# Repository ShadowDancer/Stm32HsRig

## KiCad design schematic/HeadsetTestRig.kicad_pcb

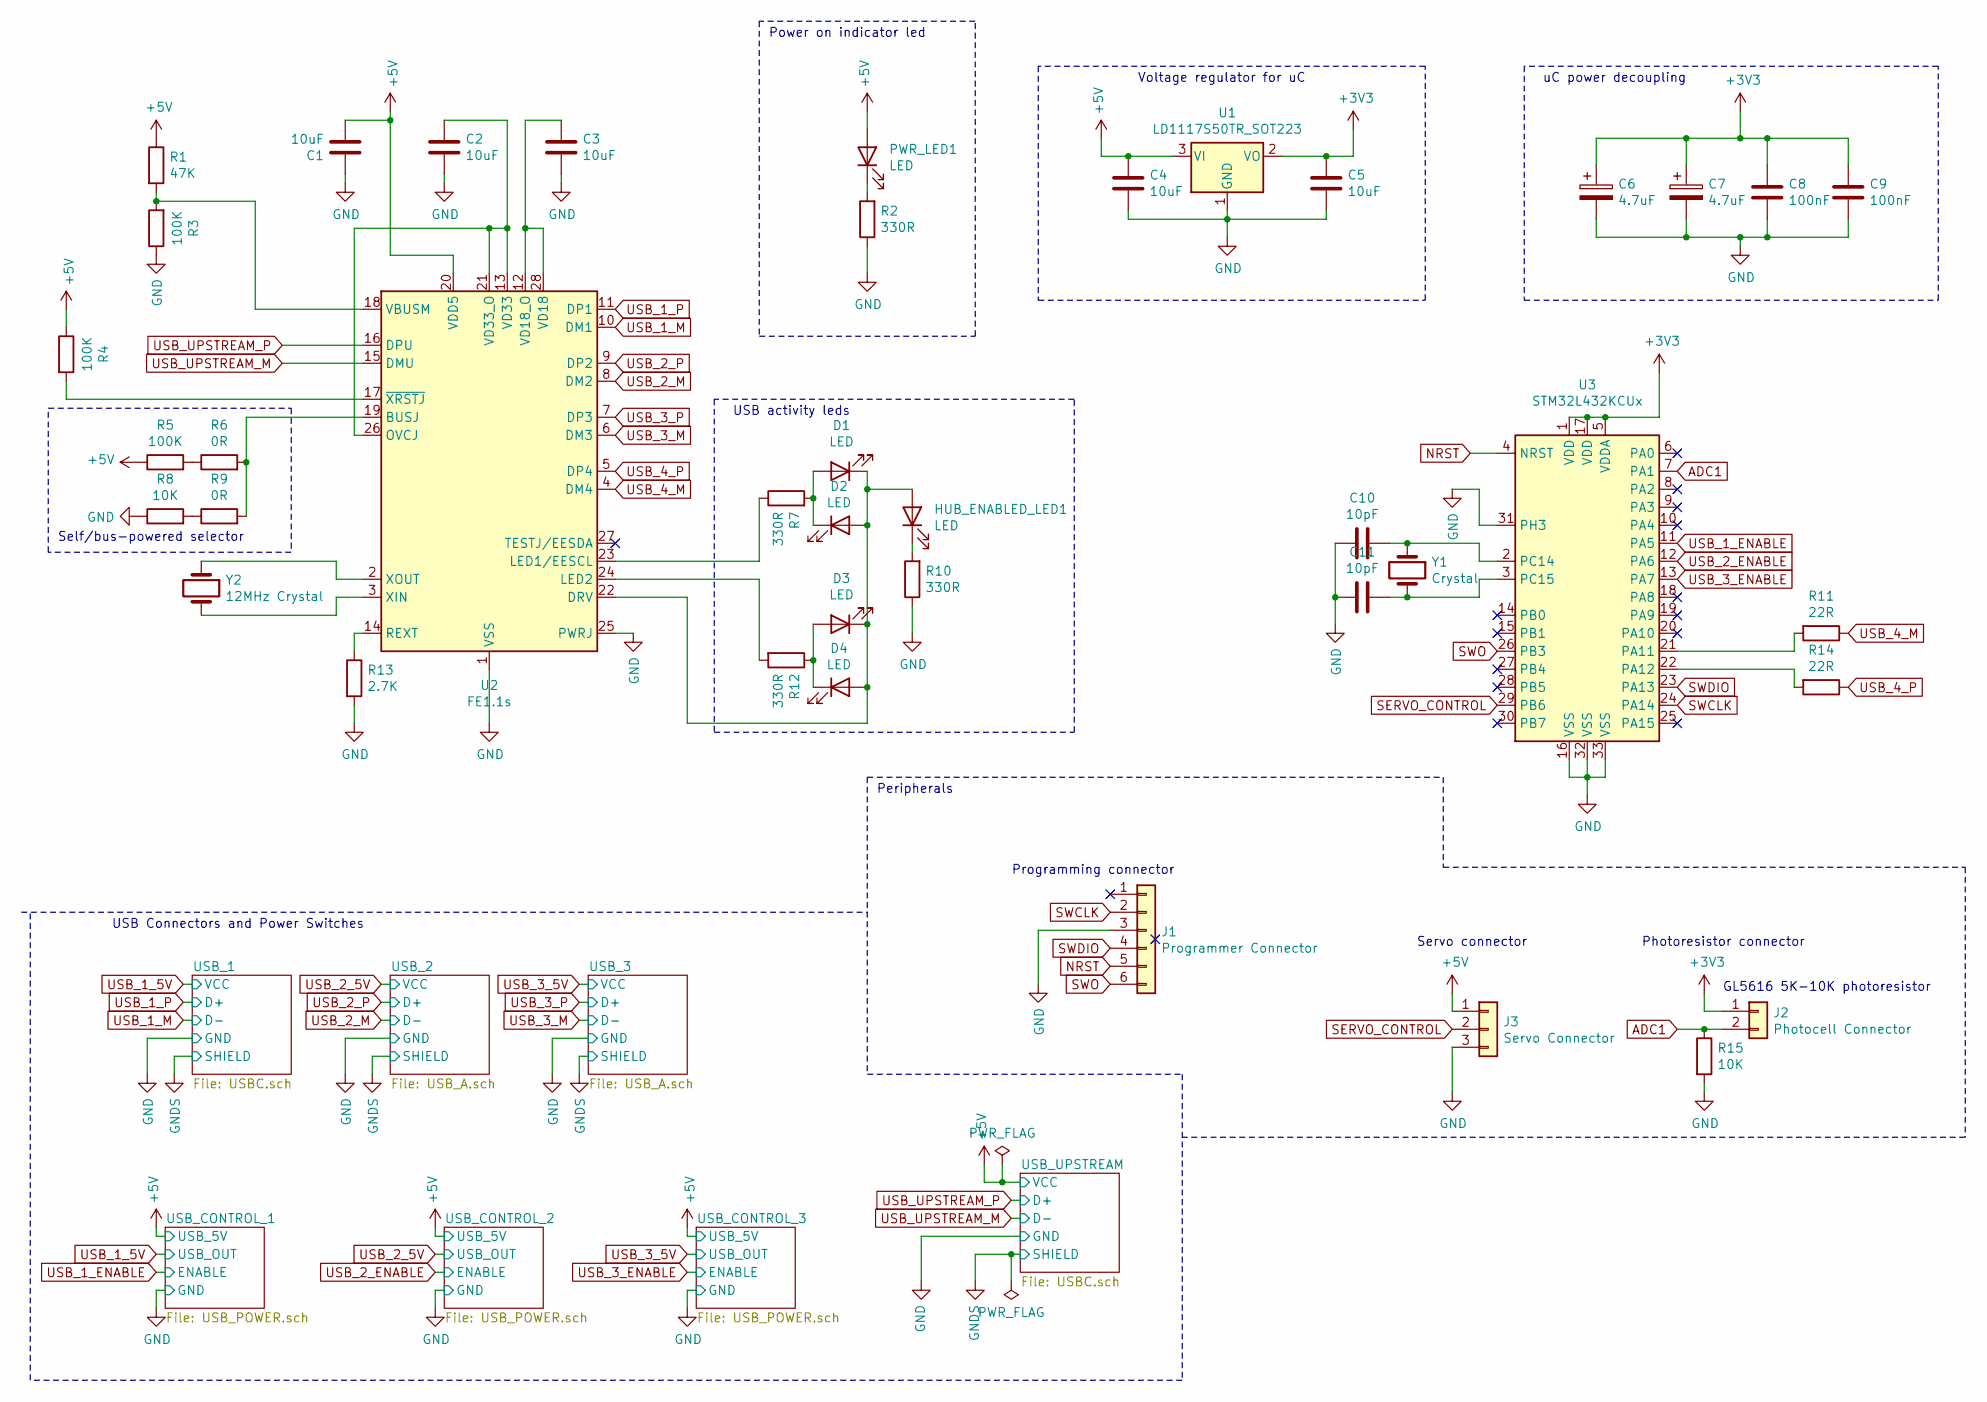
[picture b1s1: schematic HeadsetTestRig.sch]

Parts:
C1, C2, C3, C4, C5: 10uF; C_1206_3216Metric
C6, C7: 4.7uF; C_1206_3216Metric
C8, C9: 100nF; C_1206_3216Metric
C10, C11: 10pF; C_1206_3216Metric
D1, D2, D3, D4: LED; LED_1206_3216Metric
HUB_ENABLED_LED1: LED; LED_1206_3216Metric
J1: Programmer Connector; PinHeader_1x06_P2.54mm_Vertical
J2: Photocell Connector; JST_PH_B2B-PH-K_1x02_P2.00mm_Vertical
J3: Servo Connector; JST_PH_B3B-PH-K_1x03_P2.00mm_Vertical
PWR_LED1: LED; LED_1206_3216Metric
R1: 47K; R_0805_2012Metric
R2, R7, R10, R12: 330R; R_1206_3216Metric
R3, R5: 100K; R_0805_2012Metric
R4: 100K; R_1206_3216Metric
R6, R9: 0R; R_0805_2012Metric
R8: 10K; R_0805_2012Metric
R11, R14: 22R; R_1206_3216Metric
R13: 2.7K; R_0805_2012Metric
R15: 10K; R_1206_3216Metric
U1: LD1117S50TR_SOT223; SOT-223-3_TabPin2
U2: FE1.1s; SSOP-28_3.9x9.9mm_P0.635mm
U3: STM32L432KCUx; QFN-32-1EP_5x5mm_P0.5mm_EP3.45x3.45mm
Y1: Crystal; Crystal_HC49-U_Vertical
Y2: 12MHz Crystal; Crystal_HC49-U_Vertical

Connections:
+3V3: C5.1, C6.1, C7.1, C8.1, C9.1, J2.1, U1.2 (VO), U3.1 (VDD), U3.5 (VDDA), U3.17 (VDD)
+5V: C1.2, C4.1, J3.1, PWR_LED1.2 (A), R1.1, R4.1, R5.1, U1.3 (VI), U2.20 (VDD5); also elsewhere on the board
ADC1: J2.2, R15.1, U3.7 (PA1)
GND: C1.1, C2.2, C3.2, C4.2, C5.2, C6.2, C7.2, C8.2, C9.2, C10.2, C11.2, J1.3, J3.3, R2.1, R3.1, R8.1, R10.1, R13.2, R15.2, U1.1 (GND), U2.1 (VSS), U2.25 (PWRJ), U3.16 (VSS), U3.31 (PH3), U3.32 (VSS), U3.33 (VSS); also elsewhere on the board
NRST: J1.5, U3.4 (NRST)
unnamed: C2.1, U2.13 (VD33), U2.21 (VD33_O), U2.26 (OVCJ)
unnamed: C3.1, U2.12 (VD18_O), U2.28 (VD18)
unnamed: C10.1, U3.2 (PC14), Y1.1
unnamed: C11.1, U3.3 (PC15), Y1.2
unnamed: D1.1 (K), D2.2 (A), D3.1 (K), D4.2 (A), HUB_ENABLED_LED1.2 (A), U2.22 (DRV)
unnamed: D1.2 (A), D2.1 (K), R7.2
unnamed: D3.2 (A), D4.1 (K), R12.1
unnamed: HUB_ENABLED_LED1.1 (K), R10.2
unnamed: PWR_LED1.1 (K), R2.2
unnamed: R1.2, R3.2, U2.18 (VBUSM)
unnamed: R4.2, U2.17 (~XRSTJ)
unnamed: R5.2, R6.1
unnamed: R6.2, R9.2, U2.19 (BUSJ)
unnamed: R7.1, U2.23 (LED1/EESCL)
unnamed: R8.2, R9.1
unnamed: R11.2, U3.21 (PA11)
unnamed: R12.2, U2.24 (LED2)
unnamed: R13.1, U2.14 (REXT)
unnamed: R14.2, U3.22 (PA12)
unnamed: U2.2 (XOUT), Y2.1
unnamed: U2.3 (XIN), Y2.2
SERVO_CONTROL: J3.2, U3.29 (PB6)
SWCLK: J1.2, U3.24 (PA14)
SWDIO: J1.4, U3.23 (PA13)
SWO: J1.6, U3.26 (PB3)
USB_1_ENABLE: U3.11 (PA5); also elsewhere on the board
USB_1_M: U2.10 (DM1); also elsewhere on the board
USB_1_P: U2.11 (DP1); also elsewhere on the board
USB_2_ENABLE: U3.12 (PA6); also elsewhere on the board
USB_2_M: U2.8 (DM2); also elsewhere on the board
USB_2_P: U2.9 (DP2); also elsewhere on the board
USB_3_ENABLE: U3.13 (PA7); also elsewhere on the board
USB_3_M: U2.6 (DM3); also elsewhere on the board
USB_3_P: U2.7 (DP3); also elsewhere on the board
USB_4_M: R11.1, U2.4 (DM4)
USB_4_P: R14.1, U2.5 (DP4)
USB_UPSTREAM_M: U2.15 (DMU); also elsewhere on the board
USB_UPSTREAM_P: U2.16 (DPU); also elsewhere on the board

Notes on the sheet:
GL5616 5K-10K photoresistor
USB Connectors and Power Switches
Self/bus-powered selector
USB activity leds
Power on indicator led
Voltage regulator for uC
uC power decoupling
Peripherals
Programming connector
Servo connector
Photoresistor connector

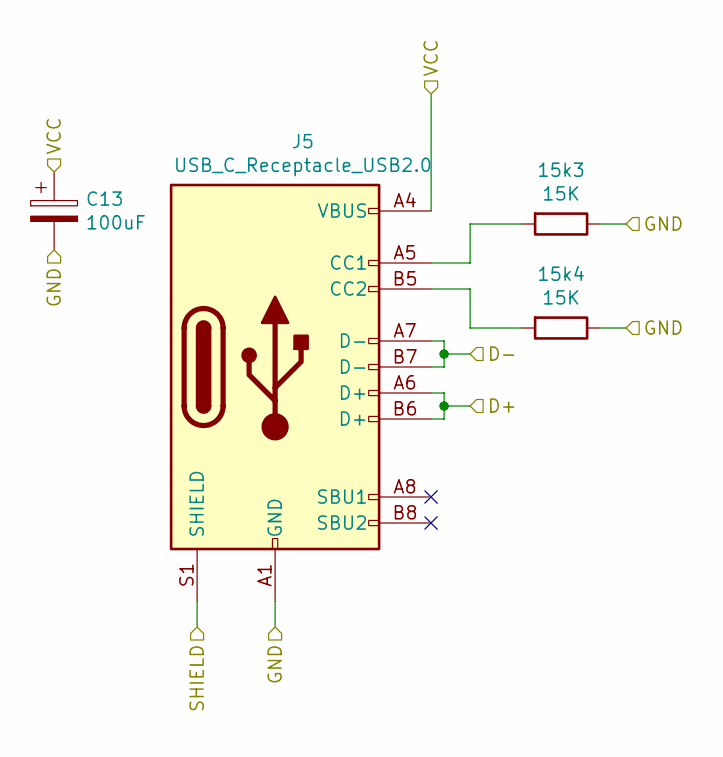
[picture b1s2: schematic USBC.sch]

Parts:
15k1, 15k2: 15K; R_0805_2012Metric
C12: 100uF; CP_Elec_6.3x5.9
J4: USB_C_Receptacle_USB2.0

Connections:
+5V: C12.1, J4.A4 (VBUS), J4.A9 (VBUS), J4.B4 (VBUS), J4.B9 (VBUS); also elsewhere on the board
GND: 15k1.1, 15k2.1, C12.2, J4.A1 (GND), J4.A12 (GND), J4.B1 (GND), J4.B12 (GND); also elsewhere on the board
GNDS: J4.S1 (SHIELD); also elsewhere on the board
unnamed: 15k1.2, J4.A5 (CC1)
unnamed: 15k2.2, J4.B5 (CC2)
USB_UPSTREAM_M: J4.A7 (D-), J4.B7 (D-); also elsewhere on the board
USB_UPSTREAM_P: J4.A6 (D+), J4.B6 (D+); also elsewhere on the board

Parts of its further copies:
15k3, 15k4: 15K; R_0805_2012Metric
C13: 100uF; CP_Elec_6.3x5.9
J5: USB_C_Receptacle_USB2.0

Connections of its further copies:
GND: 15k3.1, 15k4.1, J5.A1 (GND), J5.A12 (GND), J5.B1 (GND), J5.B12 (GND); also elsewhere on the board
GNDS: J5.S1 (SHIELD); also elsewhere on the board
unnamed: 15k3.2, J5.A5 (CC1)
unnamed: 15k4.2, J5.B5 (CC2)
USB_1_5V: J5.A4 (VBUS), J5.A9 (VBUS), J5.B4 (VBUS), J5.B9 (VBUS); also elsewhere on the board
USB_1_M: J5.A7 (D-), J5.B7 (D-); also elsewhere on the board
USB_1_P: J5.A6 (D+), J5.B6 (D+); also elsewhere on the board

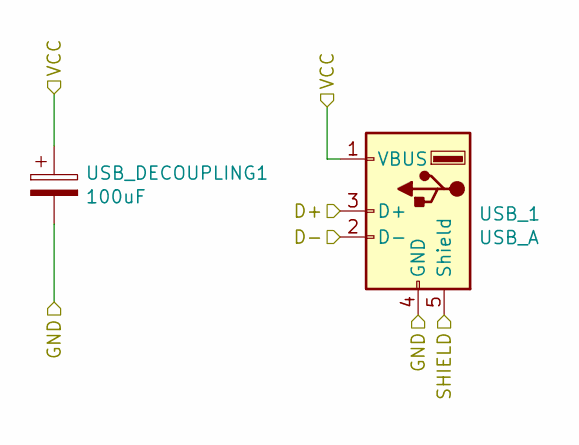
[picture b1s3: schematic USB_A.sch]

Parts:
USB_1: USB_A; USB_B_Lumberg_2411_02_Horizontal
USB_DECOUPLING1: 100uF; CP_Elec_6.3x5.9

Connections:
GND: USB_1.4 (GND), USB_DECOUPLING1.2; also elsewhere on the board
GNDS: USB_1.5 (Shield); also elsewhere on the board
USB_2_5V: USB_1.1 (VBUS), USB_DECOUPLING1.1; also elsewhere on the board
USB_2_M: USB_1.2 (D-); also elsewhere on the board
USB_2_P: USB_1.3 (D+); also elsewhere on the board

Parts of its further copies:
USB_2: USB_A; USB_B_Lumberg_2411_02_Horizontal
USB_DECOUP2: 100uF; CP_Elec_6.3x5.9

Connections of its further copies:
GND: USB_2.4 (GND), USB_DECOUP2.2; also elsewhere on the board
GNDS: USB_2.5 (Shield); also elsewhere on the board
USB_3_5V: USB_2.1 (VBUS), USB_DECOUP2.1; also elsewhere on the board
USB_3_M: USB_2.2 (D-); also elsewhere on the board
USB_3_P: USB_2.3 (D+); also elsewhere on the board

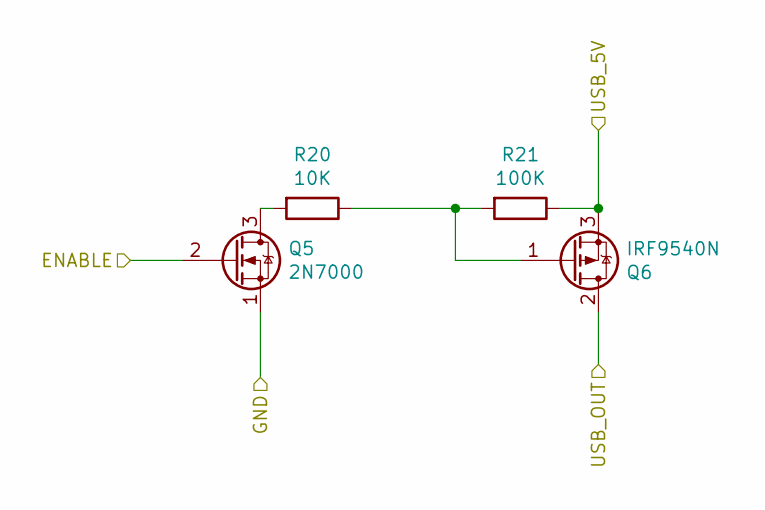
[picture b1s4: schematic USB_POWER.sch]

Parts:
Q1: 2N7000; TO-92_Inline
Q2: IRF9540N; TO-220-3_Vertical
R16: 10K; R_1206_3216Metric
R17: 100K; R_1206_3216Metric

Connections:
+5V: Q2.3 (S), R17.1; also elsewhere on the board
GND: Q1.1 (S); also elsewhere on the board
unnamed: Q1.3 (D), R16.2
unnamed: Q2.1 (G), R16.1, R17.2
USB_1_5V: Q2.2 (D); also elsewhere on the board
USB_1_ENABLE: Q1.2 (G); also elsewhere on the board

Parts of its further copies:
Q3, Q5: 2N7000; TO-92_Inline
Q4, Q6: IRF9540N; TO-220-3_Vertical
R18, R20: 10K; R_1206_3216Metric
R19, R21: 100K; R_1206_3216Metric

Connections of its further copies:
+5V: Q4.3 (S), Q6.3 (S), R19.1, R21.1; also elsewhere on the board
GND: Q3.1 (S), Q5.1 (S); also elsewhere on the board
unnamed: Q3.3 (D), R18.2
unnamed: Q4.1 (G), R18.1, R19.2
unnamed: Q5.3 (D), R20.2
unnamed: Q6.1 (G), R20.1, R21.2
USB_2_5V: Q4.2 (D); also elsewhere on the board
USB_2_ENABLE: Q3.2 (G); also elsewhere on the board
USB_3_5V: Q6.2 (D); also elsewhere on the board
USB_3_ENABLE: Q5.2 (G); also elsewhere on the board

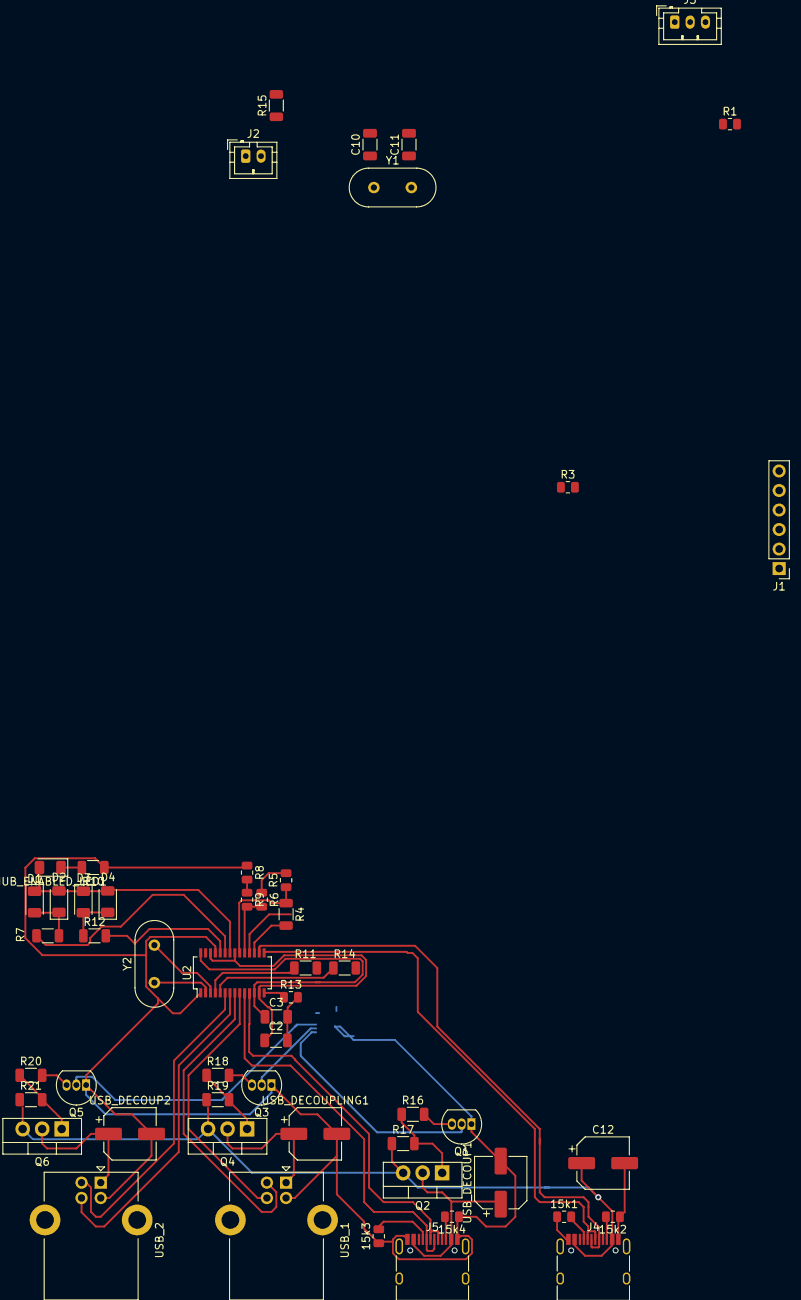
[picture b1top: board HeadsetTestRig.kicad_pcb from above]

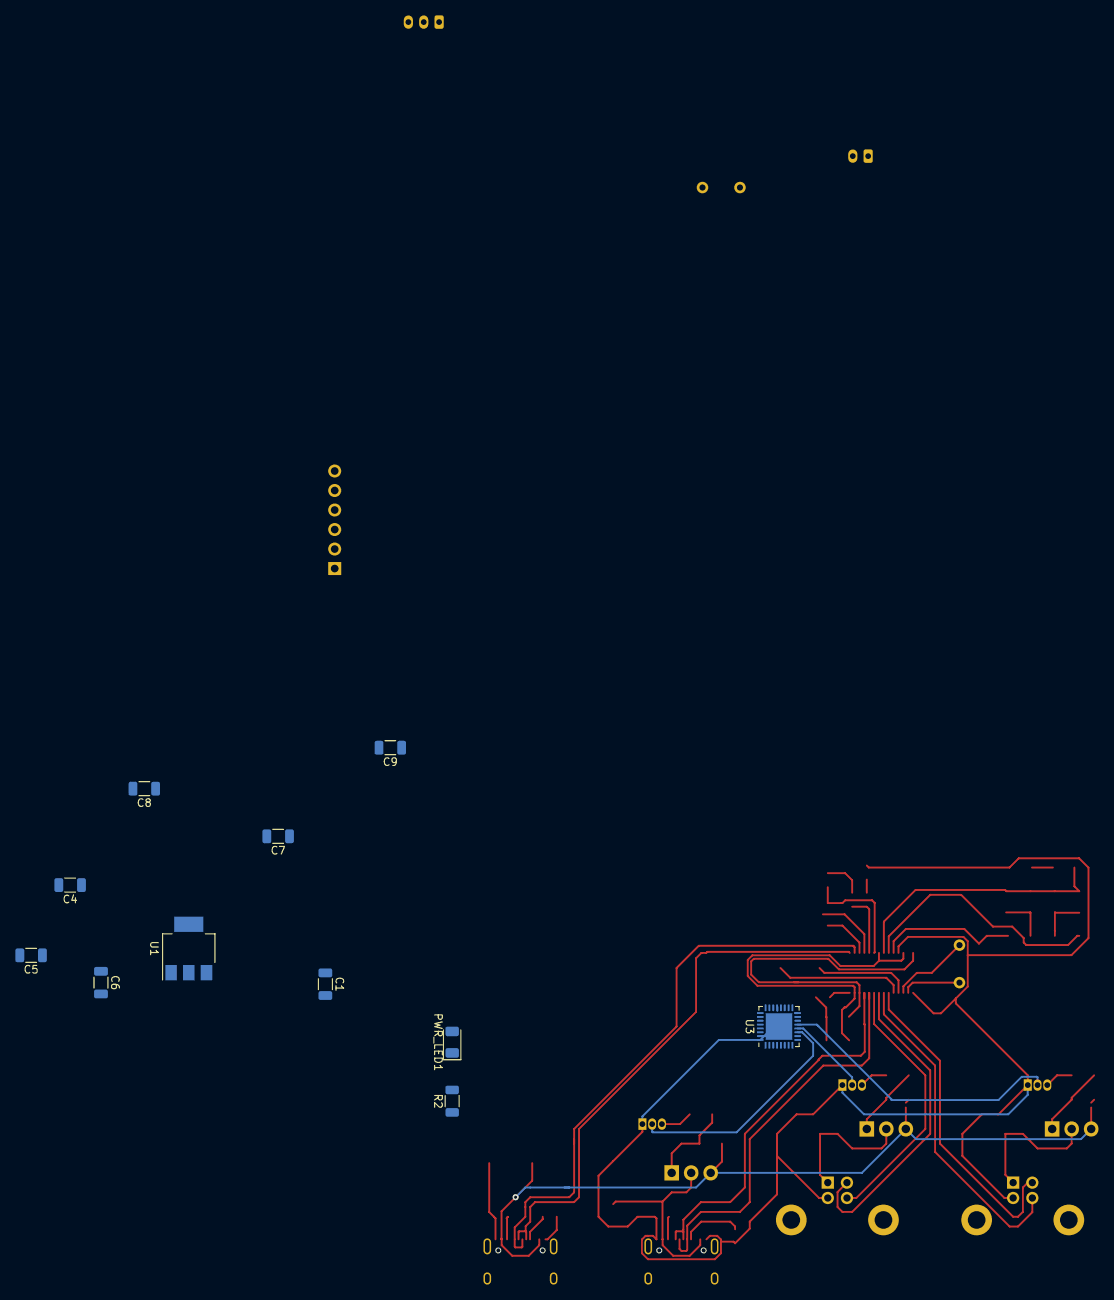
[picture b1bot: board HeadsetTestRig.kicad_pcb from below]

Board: 2 copper layers, 64 parts (11 on the bottom side), 57 nets.

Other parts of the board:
USB_DECOUP1: 100uF; CP_Elec_6.3x5.9

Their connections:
GND: USB_DECOUP1.2; also elsewhere on the board
USB_1_5V: USB_DECOUP1.1; also elsewhere on the board

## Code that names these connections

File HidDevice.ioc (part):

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Mcu.Name=STM32L432K(B-C)Ux
Mcu.Package=UFQFPN32
Mcu.UserName=STM32L432KCUx
PA0.GPIOParameters=GPIO_Label
PA0.GPIO_Label=MCO [High speed clock in]
PA0.Mode=HSE-External-Clock-Source-for-LittleOrca
PA0.Signal=RCC_CK_IN
PA1.Signal=ADCx_IN6
PA11.Mode=Device
PA11.Signal=USB_DM
PA12.Mode=Device
PA12.Signal=USB_DP
PA13\ (JTMS-SWDIO).GPIOParameters=GPIO_Label
PA13\ (JTMS-SWDIO).GPIO_Label=SWDIO
PA13\ (JTMS-SWDIO).Mode=Serial_Wire
PA13\ (JTMS-SWDIO).Signal=SYS_JTMS-SWDIO
PA14\ (JTCK-SWCLK).GPIOParameters=GPIO_Label
PA14\ (JTCK-SWCLK).GPIO_Label=SWCLK
PA14\ (JTCK-SWCLK).Mode=Serial_Wire
PA14\ (JTCK-SWCLK).Signal=SYS_JTCK-SWCLK
PA15\ (JTDI).GPIOParameters=GPIO_Label
PA15\ (JTDI).GPIO_Label=VCP_RX
PA15\ (JTDI).Mode=Asynchronous
PA15\ (JTDI).Signal=USART2_RX
PA2.GPIOParameters=GPIO_Label
PA2.GPIO_Label=VCP_TX
PA2.Mode=Asynchronous
PA2.Signal=USART2_TX
PA3.Signal=ADCx_IN8
PA4.Signal=ADCx_IN9
PA5.GPIOParameters=GPIO_Label
PA5.GPIO_Label=GIPO_PA5
PA5.Signal=GPIO_Output
PA6.GPIOParameters=GPIO_Label
PA6.GPIO_Label=GIPO_PA6
PA6.Signal=GPIO_Output
PA7.GPIOParameters=GPIO_Label
PA7.GPIO_Label=GIPO_PA7
PA7.Signal=GPIO_Output
PB0.GPIOParameters=GPIO_Speed,GPIO_Label
PB0.GPIO_Label=PWM3
PB0.GPIO_Speed=GPIO_SPEED_FREQ_HIGH
PB0.Mode=PWM Generation2 CH2N
PB0.Signal=TIM1_CH2N
PB1.GPIOParameters=GPIO_Speed,GPIO_Label
PB1.GPIO_Label=PWM0
PB1.GPIO_Speed=GPIO_SPEED_FREQ_HIGH
PB1.Mode=PWM Generation3 CH3N
PB1.Signal=TIM1_CH3N
PB3\ (JTDO-TRACESWO).GPIOParameters=GPIO_Label
PB3\ (JTDO-TRACESWO).GPIO_Label=LD3 [Green]
PB3\ (JTDO-TRACESWO).Signal=GPIO_Output
PB6.GPIOParameters=GPIO_Speed,GPIO_Label
PB6.GPIO_Label=PWM1
PB6.GPIO_Speed=GPIO_SPEED_FREQ_HIGH
PB6.Mode=PWM Generation1 CH1N
PB6.Signal=TIM16_CH1N
PC14-OSC32_IN\ (PC14).Mode=LSE-External-Oscillator
PC14-OSC32_IN\ (PC14).Signal=RCC_OSC32_IN
PC15-OSC32_OUT\ (PC15).Mode=LSE-External-Oscillator
PC15-OSC32_OUT\ (PC15).Signal=RCC_OSC32_OUT
RCC.HSE_VALUE=8000000
RCC.SYSCLKFreq_VALUE=32000000
RCC.SYSCLKSource=RCC_SYSCLKSOURCE_PLLCLK
board=NUCLEO-L432KC
boardIOC=true

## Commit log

2021-01-18 Configure HID device to 64 bytes echo payload
2021-01-20 Configure timer 16 for pwm (doesn't work)
2021-01-26 Move files to src directory
2021-01-26 Add schematic
2021-01-27 Add board, update schematic
